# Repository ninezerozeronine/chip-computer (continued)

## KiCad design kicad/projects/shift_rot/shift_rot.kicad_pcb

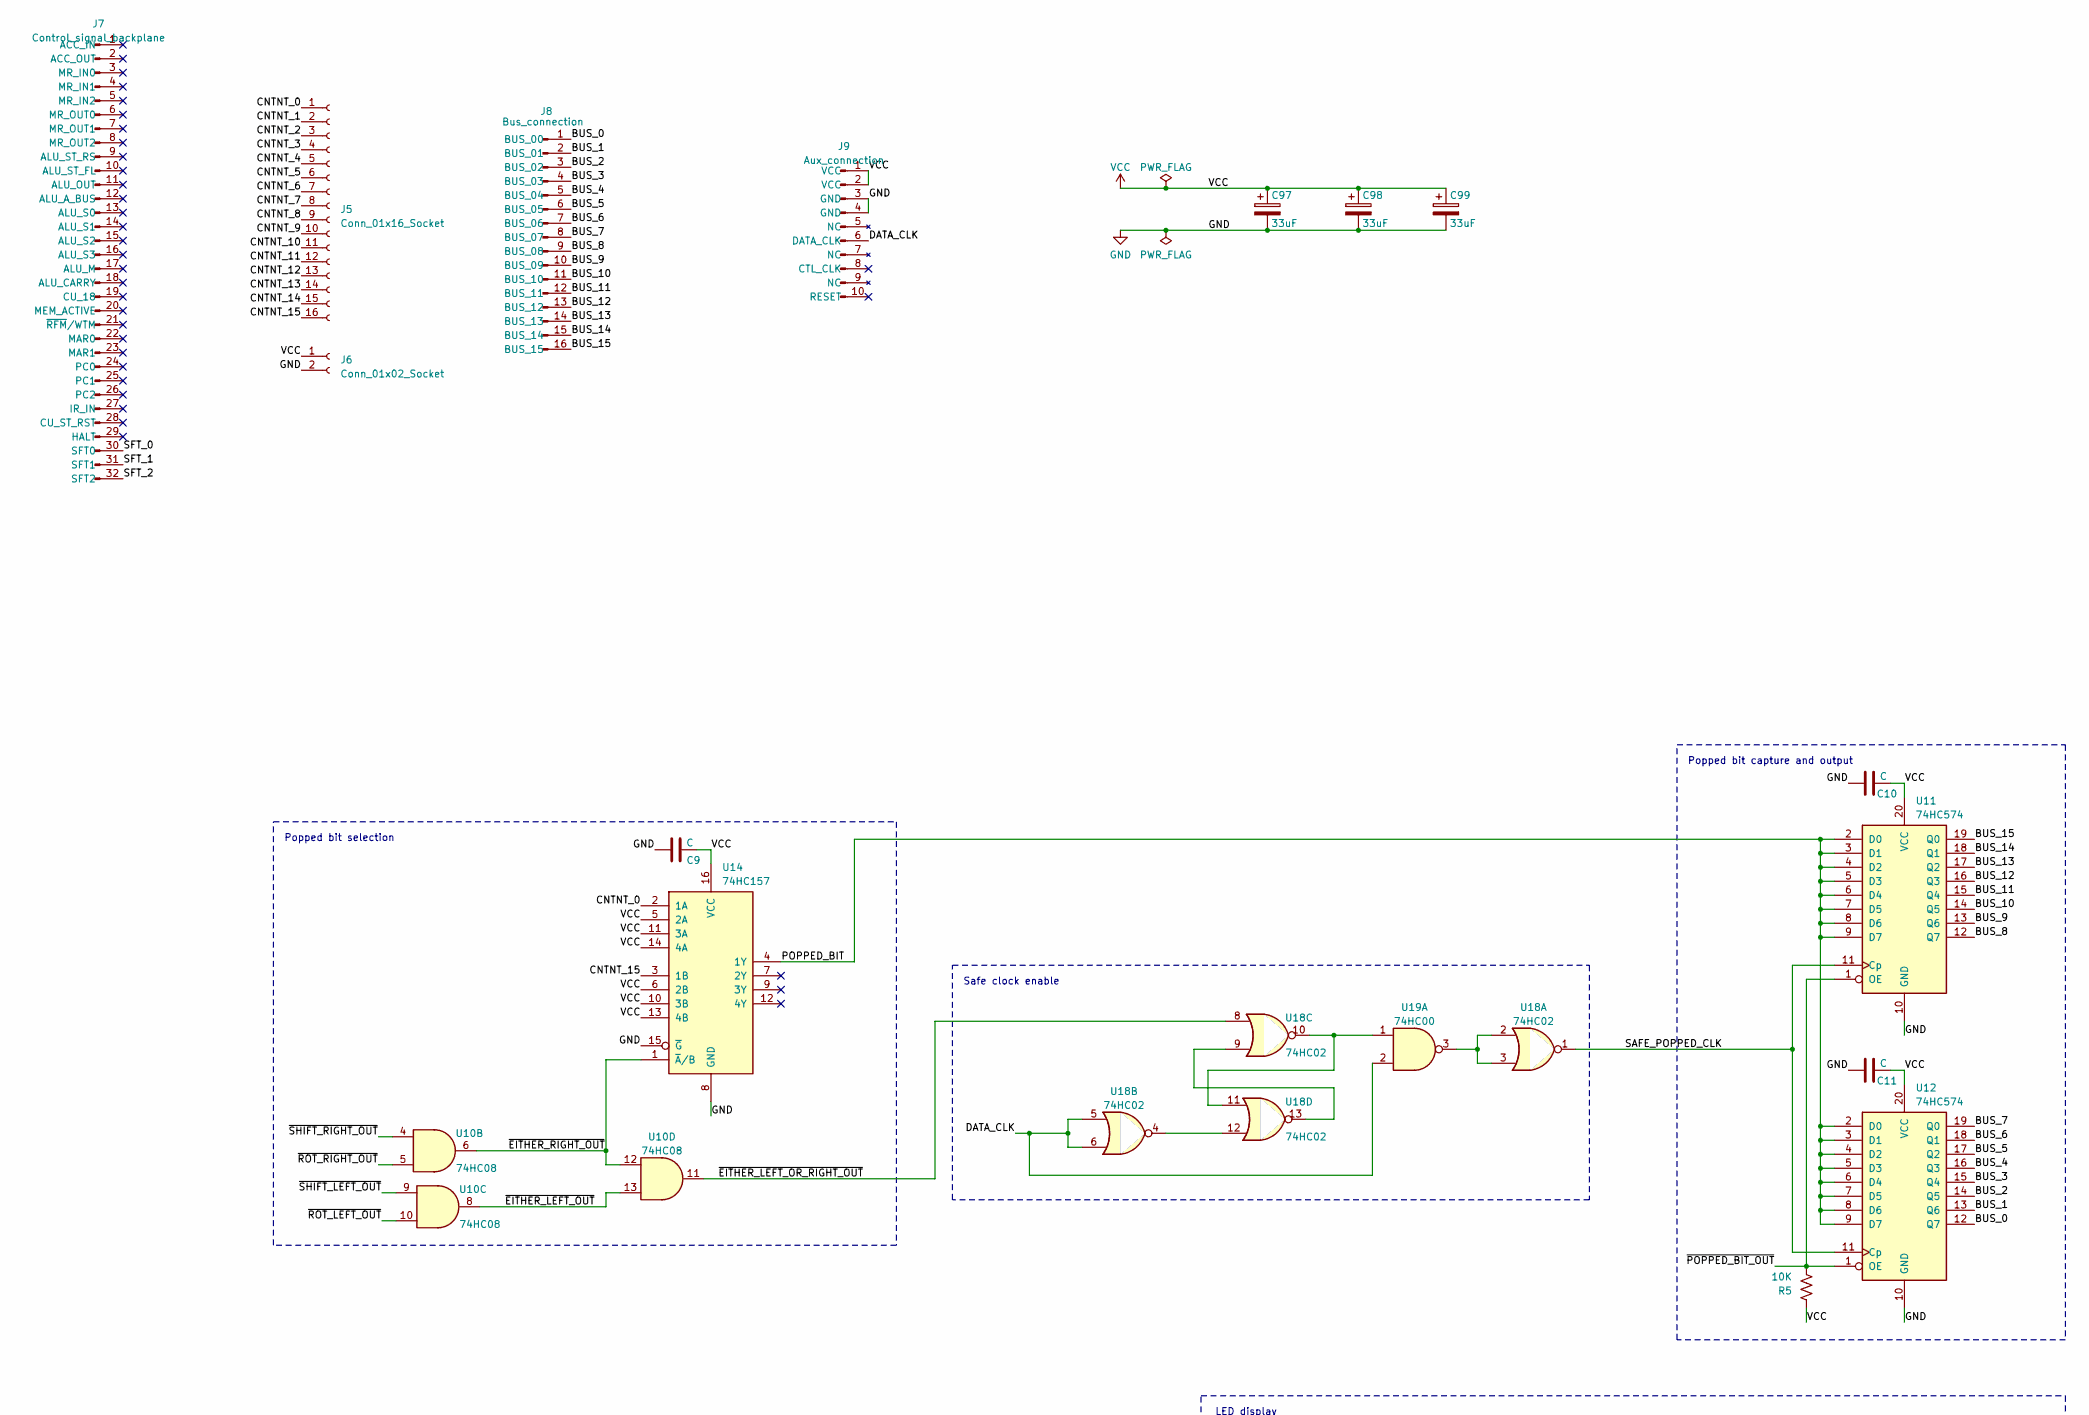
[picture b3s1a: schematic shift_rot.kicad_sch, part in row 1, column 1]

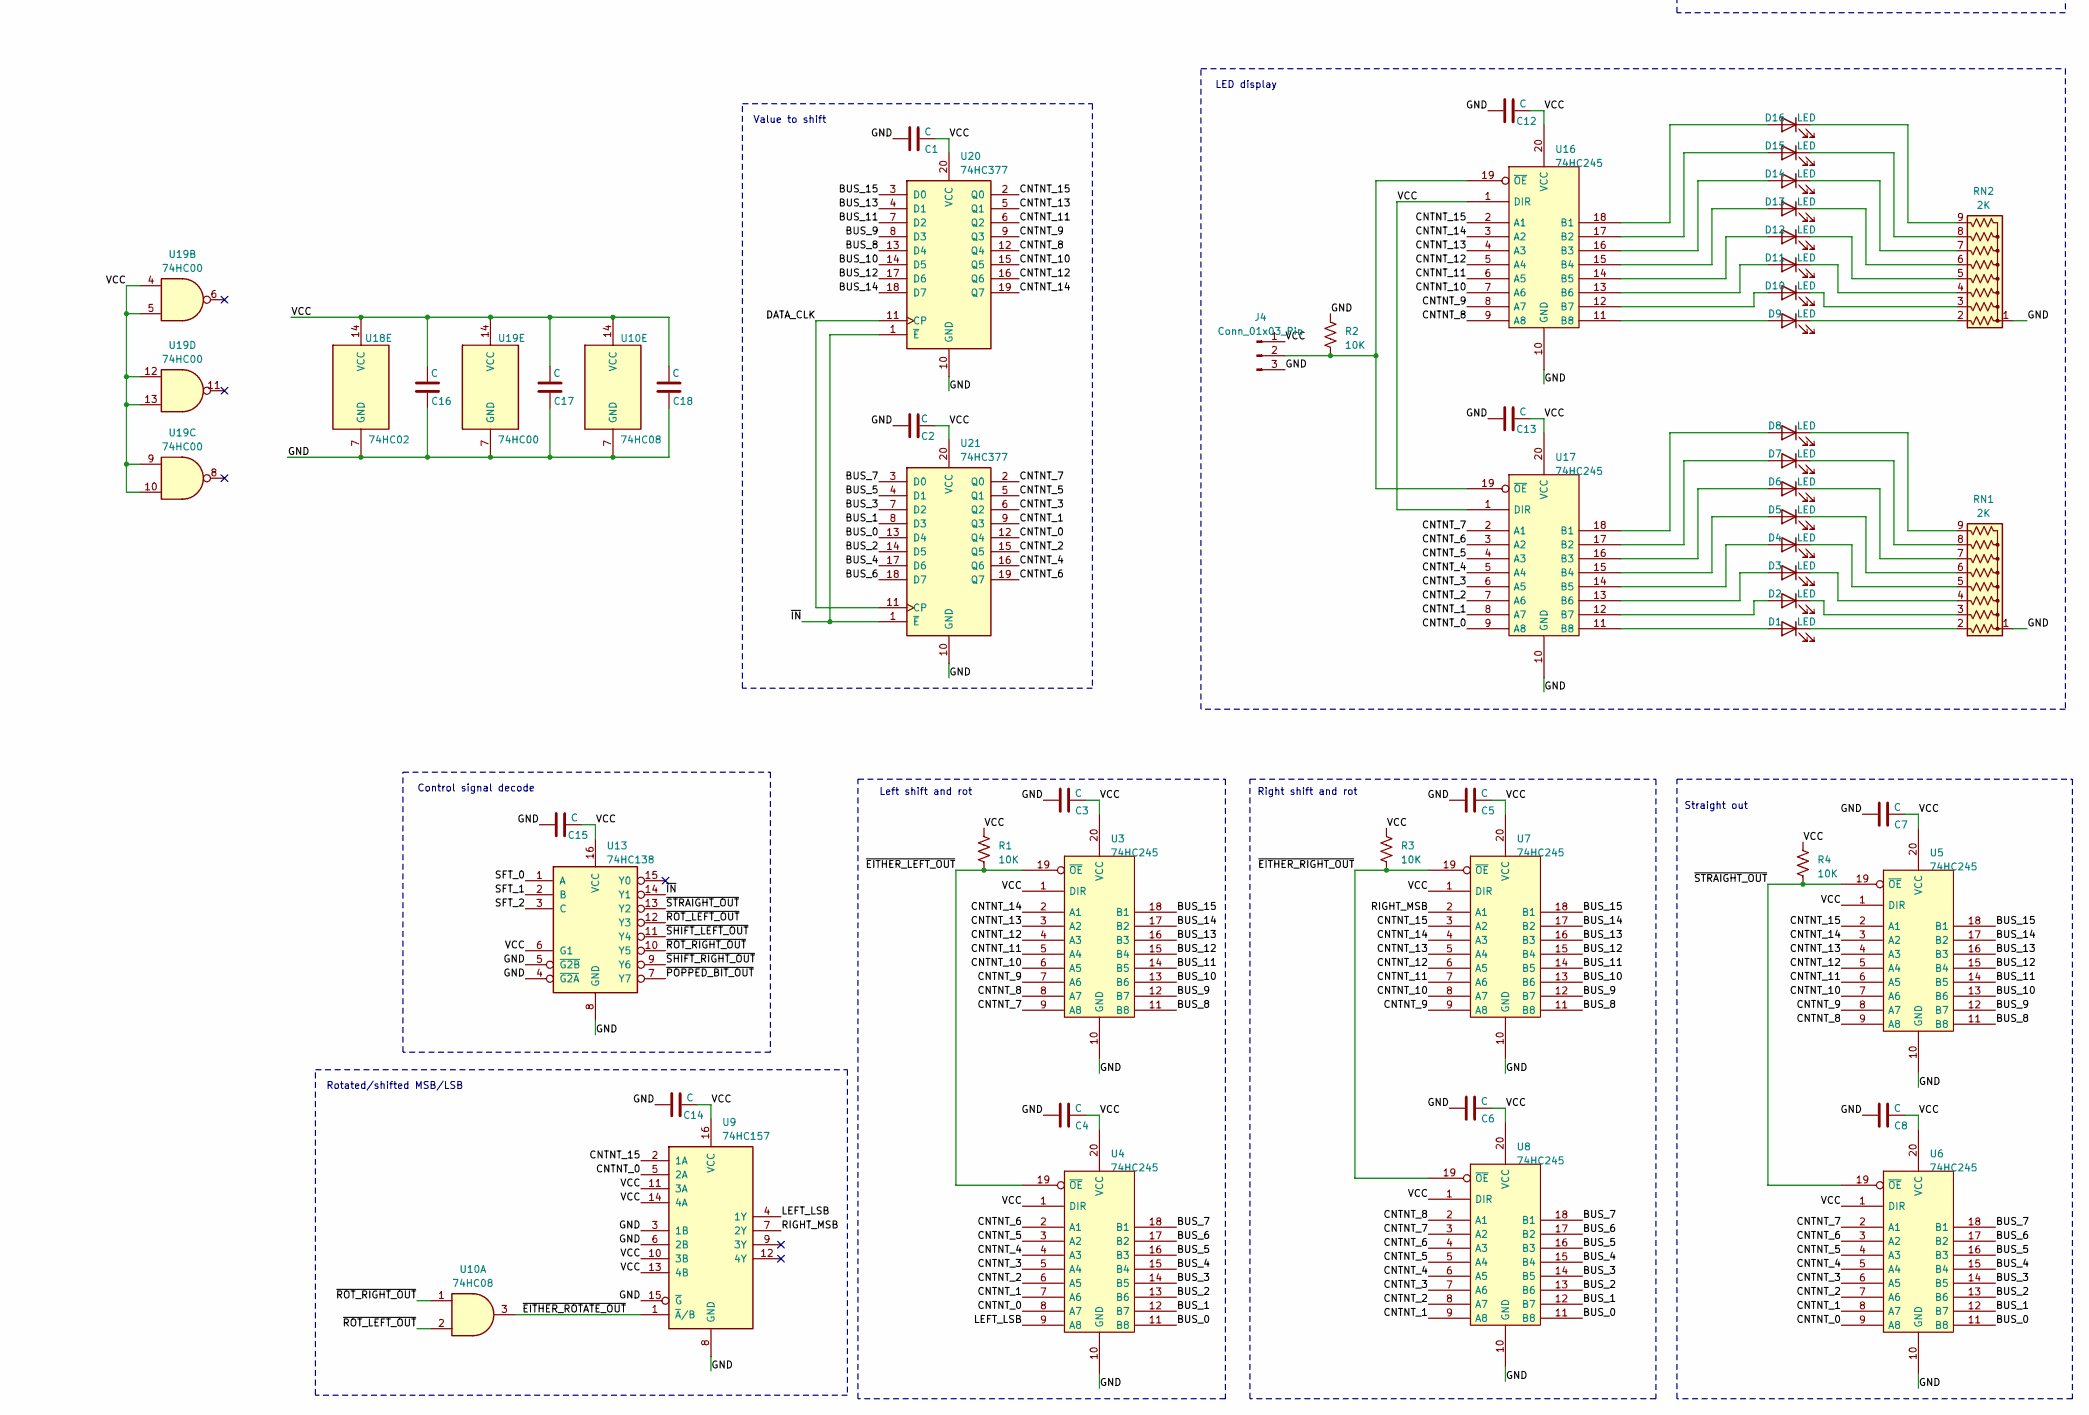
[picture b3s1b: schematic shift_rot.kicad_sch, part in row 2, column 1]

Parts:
C1, C2, C3, C4, C5, C6, C7, C8, C9, C10, C11, C12, C13, C14, C15, C16, C17, C18: C; C_Disc_D5.0mm_W2.5mm_P5.00mm
C97, C98, C99: 33uF; CP_Radial_D6.3mm_P2.50mm
D1, D2, D3, D4, D5, D6, D7, D8, D9, D10, D11, D12, D13, D14, D15, D16: LED; LED_D5.0mm_Horizontal_O3.81mm_Z3.0mm
J4: Conn_01x03_Pin; PinHeader_1x03_P2.54mm_Horizontal
J5: Conn_01x16_Socket; PinSocket_1x16_P2.54mm_Horizontal
J6: Conn_01x02_Socket; PinSocket_1x02_P2.54mm_Horizontal
J7: Control_signal_backplane; backplane-connector-single-row-annotated
J8: Bus_connection; bus-connection
J9: Aux_connection; aux-connection
R1, R2, R3, R4, R5: 10K; R_Axial_DIN0207_L6.3mm_D2.5mm_P10.16mm_Horizontal
RN1, RN2: 2K; R_Array_SIP9
U3, U4, U5, U6, U7, U8, U16, U17: 74HC245; DIP-20_W7.62mm_Socket
U9, U14: 74HC157; DIP-16_W7.62mm_Socket
U10: 74HC08; DIP-14_W7.62mm_Socket
U11, U12: 74HC574; DIP-20_W7.62mm_Socket
U13: 74HC138; DIP-16_W7.62mm_Socket
U18: 74HC02; DIP-14_W7.62mm_Socket
U19: 74HC00; DIP-14_W7.62mm_Socket
U20, U21: 74HC377; DIP-20_W7.62mm_Socket

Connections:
/BUS_0: J8.1 (BUS_00), U4.11 (B8), U6.11 (B8), U8.11 (B8), U12.12 (Q7), U21.13 (D4)
/BUS_1: J8.2 (BUS_01), U4.12 (B7), U6.12 (B7), U8.12 (B7), U12.13 (Q6), U21.8 (D3)
/BUS_2: J8.3 (BUS_02), U4.13 (B6), U6.13 (B6), U8.13 (B6), U12.14 (Q5), U21.14 (D5)
/BUS_3: J8.4 (BUS_03), U4.14 (B5), U6.14 (B5), U8.14 (B5), U12.15 (Q4), U21.7 (D2)
/BUS_4: J8.5 (BUS_04), U4.15 (B4), U6.15 (B4), U8.15 (B4), U12.16 (Q3), U21.17 (D6)
/BUS_5: J8.6 (BUS_05), U4.16 (B3), U6.16 (B3), U8.16 (B3), U12.17 (Q2), U21.4 (D1)
/BUS_6: J8.7 (BUS_06), U4.17 (B2), U6.17 (B2), U8.17 (B2), U12.18 (Q1), U21.18 (D7)
/BUS_7: J8.8 (BUS_07), U4.18 (B1), U6.18 (B1), U8.18 (B1), U12.19 (Q0), U21.3 (D0)
/BUS_8: J8.9 (BUS_08), U3.11 (B8), U5.11 (B8), U7.11 (B8), U11.12 (Q7), U20.13 (D4)
/BUS_9: J8.10 (BUS_09), U3.12 (B7), U5.12 (B7), U7.12 (B7), U11.13 (Q6), U20.8 (D3)
/BUS_10: J8.11 (BUS_10), U3.13 (B6), U5.13 (B6), U7.13 (B6), U11.14 (Q5), U20.14 (D5)
/BUS_11: J8.12 (BUS_11), U3.14 (B5), U5.14 (B5), U7.14 (B5), U11.15 (Q4), U20.7 (D2)
/BUS_12: J8.13 (BUS_12), U3.15 (B4), U5.15 (B4), U7.15 (B4), U11.16 (Q3), U20.17 (D6)
/BUS_13: J8.14 (BUS_13), U3.16 (B3), U5.16 (B3), U7.16 (B3), U11.17 (Q2), U20.4 (D1)
/BUS_14: J8.15 (BUS_14), U3.17 (B2), U5.17 (B2), U7.17 (B2), U11.18 (Q1), U20.18 (D7)
/BUS_15: J8.16 (BUS_15), U3.18 (B1), U5.18 (B1), U7.18 (B1), U11.19 (Q0), U20.3 (D0)
/CNTNT_0: J5.1, U4.8 (A7), U6.9 (A8), U9.5 (2A), U14.2 (1A), U17.9 (A8), U21.12 (Q4)
/CNTNT_1: J5.2, U4.7 (A6), U6.8 (A7), U8.9 (A8), U17.8 (A7), U21.9 (Q3)
/CNTNT_2: J5.3, U4.6 (A5), U6.7 (A6), U8.8 (A7), U17.7 (A6), U21.15 (Q5)
/CNTNT_3: J5.4, U4.5 (A4), U6.6 (A5), U8.7 (A6), U17.6 (A5), U21.6 (Q2)
/CNTNT_4: J5.5, U4.4 (A3), U6.5 (A4), U8.6 (A5), U17.5 (A4), U21.16 (Q6)
/CNTNT_5: J5.6, U4.3 (A2), U6.4 (A3), U8.5 (A4), U17.4 (A3), U21.5 (Q1)
/CNTNT_6: J5.7, U4.2 (A1), U6.3 (A2), U8.4 (A3), U17.3 (A2), U21.19 (Q7)
/CNTNT_7: J5.8, U3.9 (A8), U6.2 (A1), U8.3 (A2), U17.2 (A1), U21.2 (Q0)
/CNTNT_8: J5.9, U3.8 (A7), U5.9 (A8), U8.2 (A1), U16.9 (A8), U20.12 (Q4)
/CNTNT_9: J5.10, U3.7 (A6), U5.8 (A7), U7.9 (A8), U16.8 (A7), U20.9 (Q3)
/CNTNT_10: J5.11, U3.6 (A5), U5.7 (A6), U7.8 (A7), U16.7 (A6), U20.15 (Q5)
/CNTNT_11: J5.12, U3.5 (A4), U5.6 (A5), U7.7 (A6), U16.6 (A5), U20.6 (Q2)
/CNTNT_12: J5.13, U3.4 (A3), U5.5 (A4), U7.6 (A5), U16.5 (A4), U20.16 (Q6)
/CNTNT_13: J5.14, U3.3 (A2), U5.4 (A3), U7.5 (A4), U16.4 (A3), U20.5 (Q1)
/CNTNT_14: J5.15, U3.2 (A1), U5.3 (A2), U7.4 (A3), U16.3 (A2), U20.19 (Q7)
/CNTNT_15: J5.16, U5.2 (A1), U7.3 (A2), U9.2 (1A), U14.3 (1B), U16.2 (A1), U20.2 (Q0)
/DATA_CLK: J9.6 (DATA_CLK), U18.5, U18.6, U19.2, U20.11 (CP), U21.11 (CP)
/LEFT_LSB: U4.9 (A8), U9.4 (1Y)
/POPPED_BIT: U11.2 (D0), U11.3 (D1), U11.4 (D2), U11.5 (D3), U11.6 (D4), U11.7 (D5), U11.8 (D6), U11.9 (D7), U12.2 (D0), U12.3 (D1), U12.4 (D2), U12.5 (D3), U12.6 (D4), U12.7 (D5), U12.8 (D6), U12.9 (D7), U14.4 (1Y)
/RIGHT_MSB: U7.2 (A1), U9.7 (2Y)
/SAFE_POPPED_CLK: U11.11 (Cp), U12.11 (Cp), U18.1
/SFT_0: J7.30 (SFT0), U13.1 (A)
/SFT_1: J7.31 (SFT1), U13.2 (B)
/SFT_2: J7.32 (SFT2), U13.3 (C)
/~EITHER_LEFT_OR_RIGHT_OUT: U10.11, U18.8
/~EITHER_LEFT_OUT: R1.2, U3.19 (~OE), U4.19 (~OE), U10.8, U10.13
/~EITHER_RIGHT_OUT: R3.2, U7.19 (~OE), U8.19 (~OE), U10.6, U10.12, U14.1 (~A/B)
/~EITHER_ROTATE_OUT: U9.1 (~A/B), U10.3
/~IN: U13.14 (Y1), U20.1 (~E), U21.1 (~E)
/~POPPED_BIT_OUT: R5.2, U11.1 (OE), U12.1 (OE), U13.7 (Y7)
/~ROT_LEFT_OUT: U10.2, U10.10, U13.12 (Y3)
/~ROT_RIGHT_OUT: U10.1, U10.5, U13.10 (Y5)
/~SHIFT_LEFT_OUT: U10.9, U13.11 (Y4)
/~SHIFT_RIGHT_OUT: U10.4, U13.9 (Y6)
/~STRAIGHT_OUT: R4.2, U5.19 (~OE), U6.19 (~OE), U13.13 (Y2)
GND: C1.1, C2.1, C3.1, C4.1, C5.1, C6.1, C7.1, C8.1, C9.1, C10.1, C11.1, C12.1, C13.1, C14.1, C15.1, C16.1, C17.1, C18.1, C97.2, C98.2, C99.2, J4.3, J6.2, J9.3 (GND), J9.4 (GND), R2.1, RN1.1 (common), RN2.1 (common), U3.10 (GND), U4.10 (GND), U5.10 (GND), U6.10 (GND), U7.10 (GND), U8.10 (GND), U9.3 (1B), U9.6 (2B), U9.8 (GND), U9.15 (~G), U10.7 (GND), U11.10 (GND), U12.10 (GND), U13.4 (~G2A), U13.5 (~G2B), U13.8 (GND), U14.8 (GND), U14.15 (~G), U16.10 (GND), U17.10 (GND), U18.7 (GND), U19.7 (GND), U20.10 (GND), U21.10 (GND)
unnamed: D1.2 (A), U17.11 (B8)
unnamed: D1.1 (K), RN1.2 (R1)
unnamed: D2.2 (A), U17.12 (B7)
unnamed: D2.1 (K), RN1.3 (R2)
unnamed: D3.2 (A), U17.13 (B6)
unnamed: D3.1 (K), RN1.4 (R3)
unnamed: D4.2 (A), U17.14 (B5)
unnamed: D4.1 (K), RN1.5 (R4)
unnamed: D5.2 (A), U17.15 (B4)
unnamed: D5.1 (K), RN1.6 (R5)
unnamed: D6.2 (A), U17.16 (B3)
unnamed: D6.1 (K), RN1.7 (R6)
unnamed: D7.2 (A), U17.17 (B2)
unnamed: D7.1 (K), RN1.8 (R7)
unnamed: D8.2 (A), U17.18 (B1)
unnamed: D8.1 (K), RN1.9 (R8)
unnamed: D9.2 (A), U16.11 (B8)
unnamed: D9.1 (K), RN2.2 (R1)
unnamed: D10.2 (A), U16.12 (B7)
unnamed: D10.1 (K), RN2.3 (R2)
unnamed: D11.2 (A), U16.13 (B6)
unnamed: D11.1 (K), RN2.4 (R3)
unnamed: D12.2 (A), U16.14 (B5)
unnamed: D12.1 (K), RN2.5 (R4)
unnamed: D13.2 (A), U16.15 (B4)
unnamed: D13.1 (K), RN2.6 (R5)
unnamed: D14.2 (A), U16.16 (B3)
unnamed: D14.1 (K), RN2.7 (R6)
unnamed: D15.2 (A), U16.17 (B2)
unnamed: D15.1 (K), RN2.8 (R7)
unnamed: D16.2 (A), U16.18 (B1)
unnamed: D16.1 (K), RN2.9 (R8)
unnamed: J4.2, R2.2, U16.19 (~OE), U17.19 (~OE)
unnamed: U18.2, U18.3, U19.3
unnamed: U18.10, U18.11, U19.1
unnamed: U18.4, U18.12
unnamed: U18.9, U18.13
VCC: C1.2, C2.2, C3.2, C4.2, C5.2, C6.2, C7.2, C8.2, C9.2, C10.2, C11.2, C12.2, C13.2, C14.2, C15.2, C16.2, C17.2, C18.2, C97.1, C98.1, C99.1, J4.1, J6.1, J9.1 (VCC), J9.2 (VCC), R1.1, R3.1, R4.1, R5.1, U3.1 (DIR), U3.20 (VCC), U4.1 (DIR), U4.20 (VCC), U5.1 (DIR), U5.20 (VCC), U6.1 (DIR), U6.20 (VCC), U7.1 (DIR), U7.20 (VCC), U8.1 (DIR), U8.20 (VCC), U9.10 (3B), U9.11 (3A), U9.13 (4B), U9.14 (4A), U9.16 (VCC), U10.14 (VCC), U11.20 (VCC), U12.20 (VCC), U13.6 (G1), U13.16 (VCC), U14.5 (2A), U14.6 (2B), U14.10 (3B), U14.11 (3A), U14.13 (4B), U14.14 (4A), U14.16 (VCC), U16.1 (DIR), U16.20 (VCC), U17.1 (DIR), U17.20 (VCC), U18.14 (VCC), U19.4, U19.5, U19.9, U19.10, U19.12, U19.13, U19.14 (VCC), U20.20 (VCC), U21.20 (VCC)

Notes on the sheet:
Control signal decode
Safe clock enable
Value to shift
Rotated/shifted MSB/LSB
Left shift and rot
Straight out
Right shift and rot
LED display
Popped bit capture and output
Popped bit selection

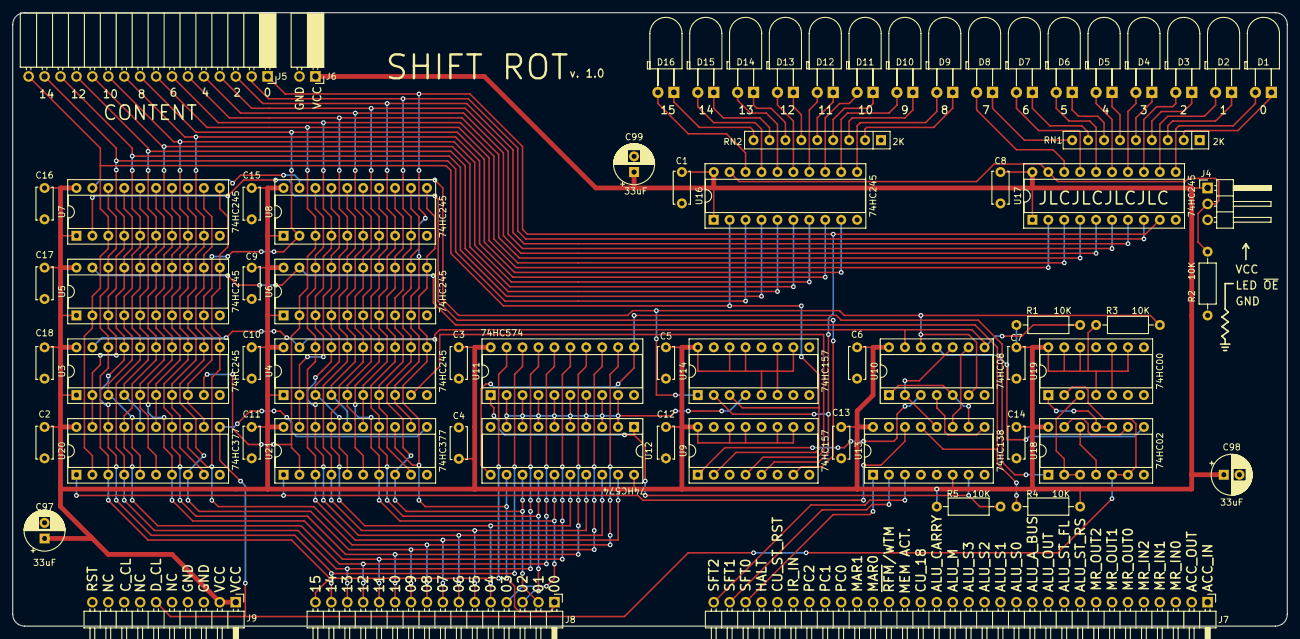
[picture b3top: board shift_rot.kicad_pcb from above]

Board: 2 copper layers, 203.2 x 97.8 mm, 68 parts (0 on the bottom side), 90 nets.

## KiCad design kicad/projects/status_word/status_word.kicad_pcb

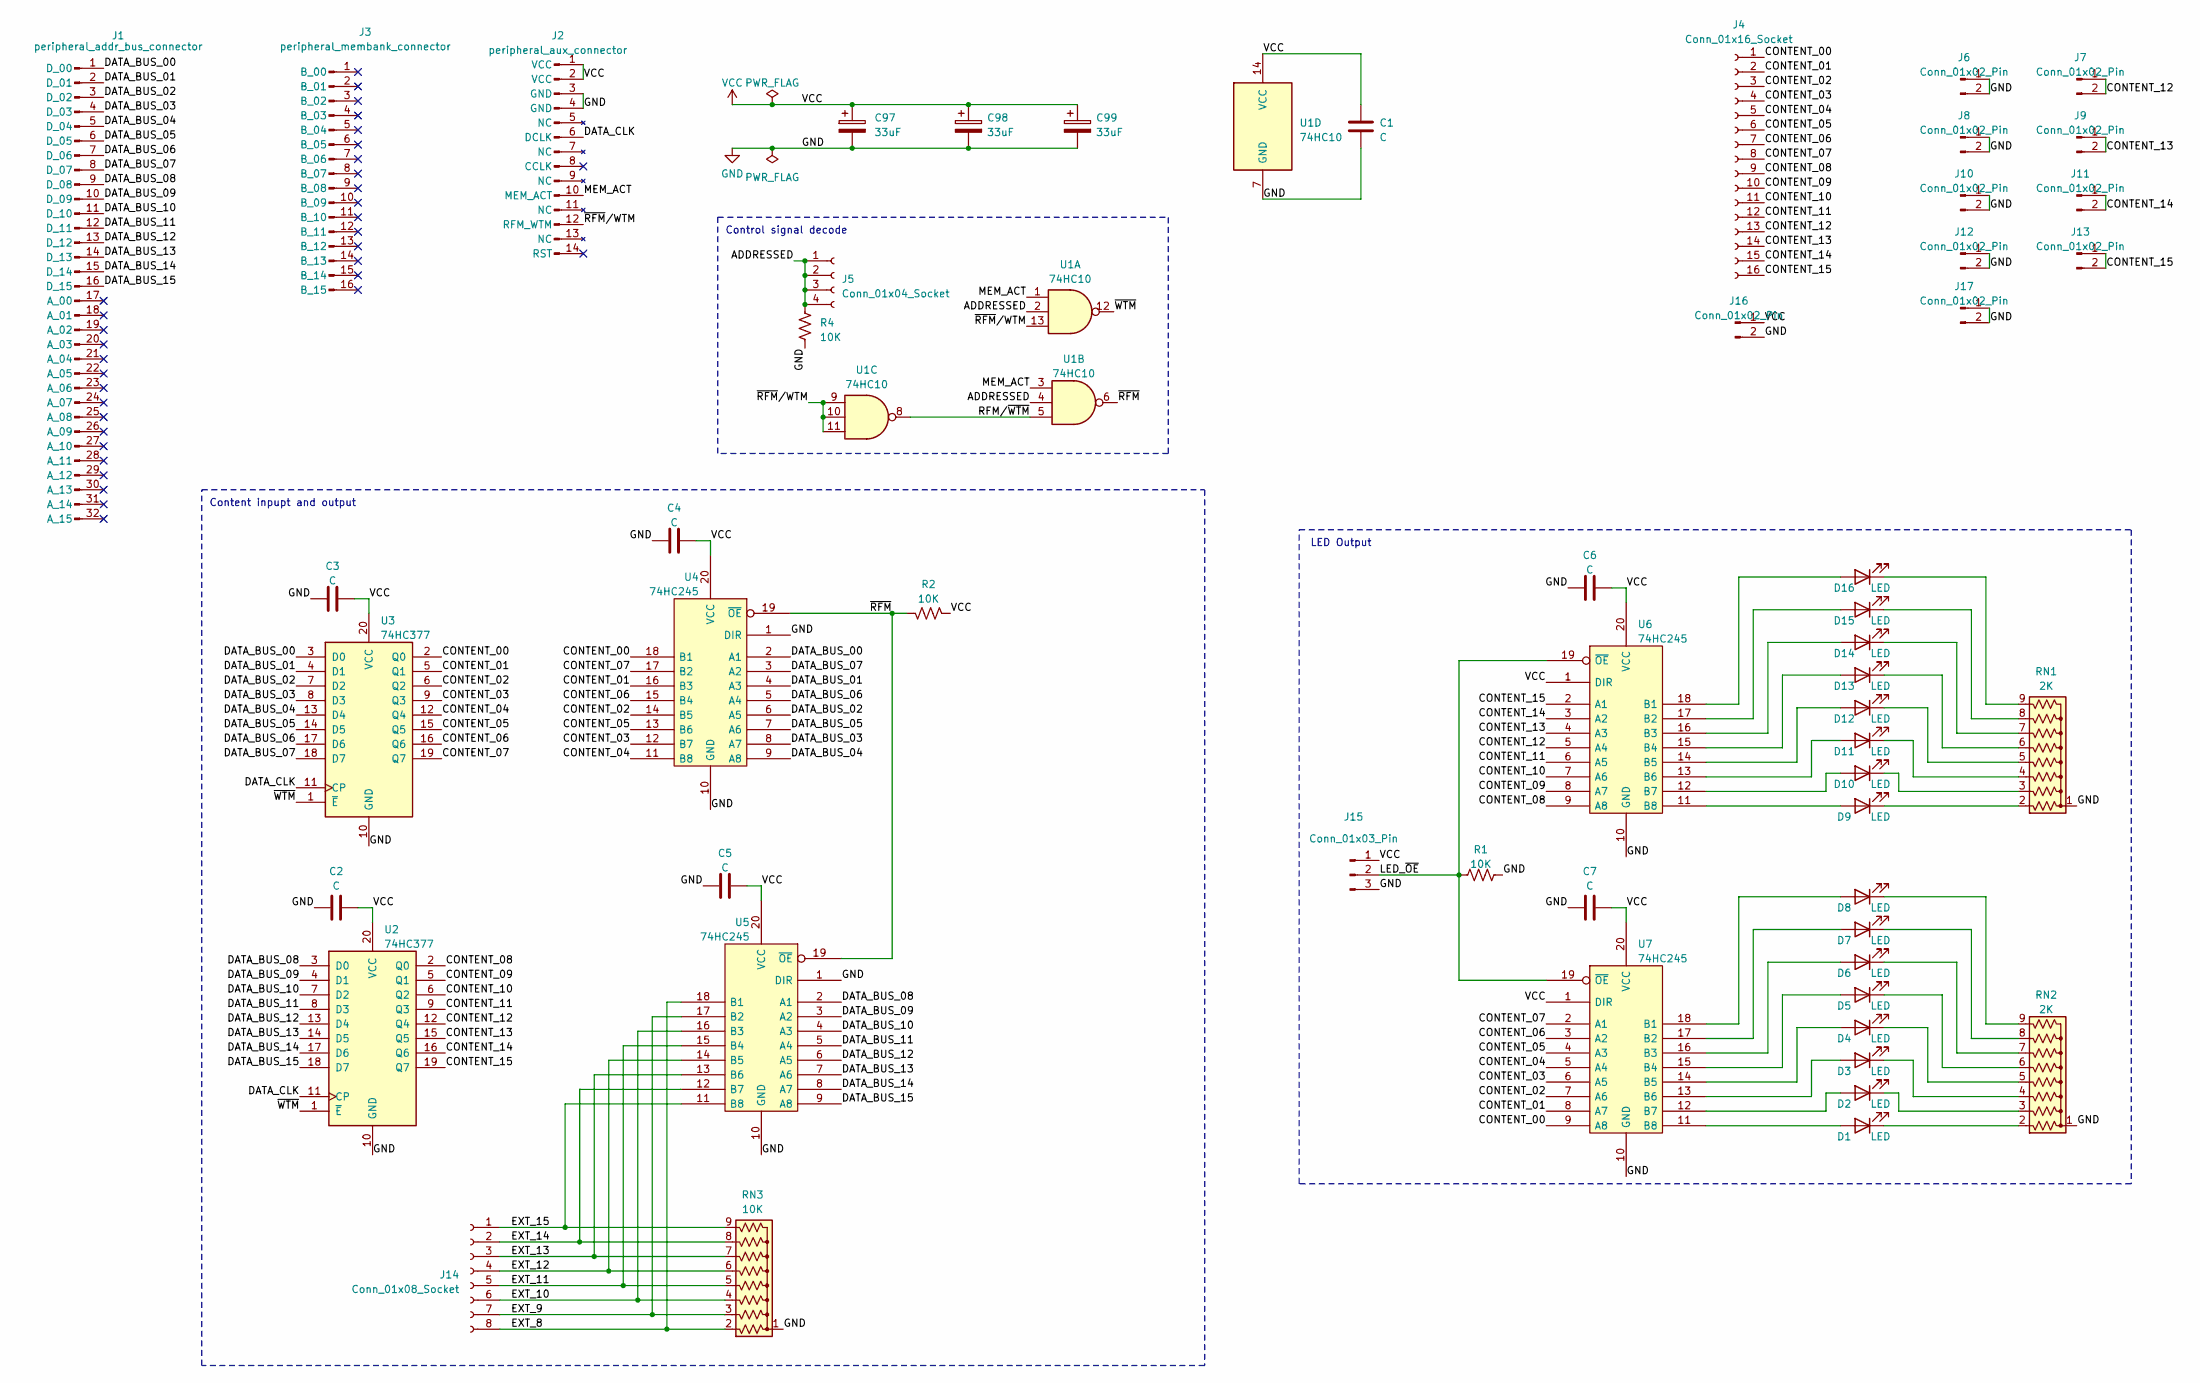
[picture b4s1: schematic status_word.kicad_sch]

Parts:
C1, C2, C3, C4, C5, C6, C7: C; C_Disc_D5.0mm_W2.5mm_P5.00mm
C97, C98, C99: 33uF; CP_Radial_D6.3mm_P2.50mm
D1, D2, D3, D4, D5, D6, D7, D8, D9, D10, D11, D12, D13, D14, D15, D16: LED; LED_D5.0mm_Horizontal_O3.81mm_Z3.0mm
J1: peripheral_addr_bus_connector; peripheral-backplane-data-addr-anno
J2: peripheral_aux_connector; peripheral-backplane-aux
J3: peripheral_membank_connector; peripheral-backplane-membank
J4: Conn_01x16_Socket; PinSocket_1x16_P2.54mm_Horizontal
J5: Conn_01x04_Socket; PinSocket_1x04_P2.54mm_Horizontal
J6, J7, J8, J9, J10, J11, J12, J13, J17: Conn_01x02_Pin; PinHeader_1x02_P2.54mm_Vertical
J14: Conn_01x08_Socket; PinSocket_1x08_P2.54mm_Horizontal
J15: Conn_01x03_Pin; PinHeader_1x03_P2.54mm_Horizontal
J16: Conn_01x02_Pin; PinSocket_1x02_P2.54mm_Horizontal
R1, R2, R4: 10K; R_Axial_DIN0207_L6.3mm_D2.5mm_P10.16mm_Horizontal
RN1, RN2: 2K; R_Array_SIP9
RN3: 10K; R_Array_SIP9
U1: 74HC10; DIP-14_W7.62mm_Socket
U2, U3: 74HC377; DIP-20_W7.62mm_Socket
U4, U5, U6, U7: 74HC245; DIP-20_W7.62mm_Socket

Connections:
/ADDRESSED: J5.1, J5.2, J5.3, J5.4, R4.1, U1.2, U1.4
/CONTENT_00: J4.1, U3.2 (Q0), U4.18 (B1), U7.9 (A8)
/CONTENT_01: J4.2, U3.5 (Q1), U4.16 (B3), U7.8 (A7)
/CONTENT_02: J4.3, U3.6 (Q2), U4.14 (B5), U7.7 (A6)
/CONTENT_03: J4.4, U3.9 (Q3), U4.12 (B7), U7.6 (A5)
/CONTENT_04: J4.5, U3.12 (Q4), U4.11 (B8), U7.5 (A4)
/CONTENT_05: J4.6, U3.15 (Q5), U4.13 (B6), U7.4 (A3)
/CONTENT_06: J4.7, U3.16 (Q6), U4.15 (B4), U7.3 (A2)
/CONTENT_07: J4.8, U3.19 (Q7), U4.17 (B2), U7.2 (A1)
/CONTENT_08: J4.9, U2.2 (Q0), U6.9 (A8)
/CONTENT_09: J4.10, U2.5 (Q1), U6.8 (A7)
/CONTENT_10: J4.11, U2.6 (Q2), U6.7 (A6)
/CONTENT_11: J4.12, U2.9 (Q3), U6.6 (A5)
/CONTENT_12: J4.13, J7.1, J7.2, U2.12 (Q4), U6.5 (A4)
/CONTENT_13: J4.14, J9.1, J9.2, U2.15 (Q5), U6.4 (A3)
/CONTENT_14: J4.15, J11.1, J11.2, U2.16 (Q6), U6.3 (A2)
/CONTENT_15: J4.16, J13.1, J13.2, U2.19 (Q7), U6.2 (A1)
/DATA_BUS_00: J1.1 (D_00), U3.3 (D0), U4.2 (A1)
/DATA_BUS_01: J1.2 (D_01), U3.4 (D1), U4.4 (A3)
/DATA_BUS_02: J1.3 (D_02), U3.7 (D2), U4.6 (A5)
/DATA_BUS_03: J1.4 (D_03), U3.8 (D3), U4.8 (A7)
/DATA_BUS_04: J1.5 (D_04), U3.13 (D4), U4.9 (A8)
/DATA_BUS_05: J1.6 (D_05), U3.14 (D5), U4.7 (A6)
/DATA_BUS_06: J1.7 (D_06), U3.17 (D6), U4.5 (A4)
/DATA_BUS_07: J1.8 (D_07), U3.18 (D7), U4.3 (A2)
/DATA_BUS_08: J1.9 (D_08), U2.3 (D0), U5.2 (A1)
/DATA_BUS_09: J1.10 (D_09), U2.4 (D1), U5.3 (A2)
/DATA_BUS_10: J1.11 (D_10), U2.7 (D2), U5.4 (A3)
/DATA_BUS_11: J1.12 (D_11), U2.8 (D3), U5.5 (A4)
/DATA_BUS_12: J1.13 (D_12), U2.13 (D4), U5.6 (A5)
/DATA_BUS_13: J1.14 (D_13), U2.14 (D5), U5.7 (A6)
/DATA_BUS_14: J1.15 (D_14), U2.17 (D6), U5.8 (A7)
/DATA_BUS_15: J1.16 (D_15), U2.18 (D7), U5.9 (A8)
/DATA_CLK: J2.6 (DCLK), U2.11 (CP), U3.11 (CP)
/EXT_8: J14.8, RN3.2 (R1), U5.18 (B1)
/EXT_9: J14.7, RN3.3 (R2), U5.17 (B2)
/EXT_10: J14.6, RN3.4 (R3), U5.16 (B3)
/EXT_11: J14.5, RN3.5 (R4), U5.15 (B4)
/EXT_12: J14.4, RN3.6 (R5), U5.14 (B5)
/EXT_13: J14.3, RN3.7 (R6), U5.13 (B6)
/EXT_14: J14.2, RN3.8 (R7), U5.12 (B7)
/EXT_15: J14.1, RN3.9 (R8), U5.11 (B8)
/LED_~OE: J15.2, R1.2, U6.19 (~OE), U7.19 (~OE)
/MEM_ACT: J2.10 (MEM_ACT), U1.1, U1.3
/RFM/~WTM: U1.5, U1.8
/~RFM: R2.2, U1.6, U4.19 (~OE), U5.19 (~OE)
/~RFM/WTM: J2.12 (RFM_WTM), U1.9, U1.10, U1.11, U1.13
/~WTM: U1.12, U2.1 (~E), U3.1 (~E)
GND: C1.2, C2.1, C3.1, C4.1, C5.1, C6.1, C7.1, C97.2, C98.2, C99.2, J2.3 (GND), J2.4 (GND), J6.1, J6.2, J8.1, J8.2, J10.1, J10.2, J12.1, J12.2, J15.3, J16.2, J17.1, J17.2, R1.1, R4.2, RN1.1 (common), RN2.1 (common), RN3.1 (common), U1.7 (GND), U2.10 (GND), U3.10 (GND), U4.1 (DIR), U4.10 (GND), U5.1 (DIR), U5.10 (GND), U6.10 (GND), U7.10 (GND)
unnamed: D1.2 (A), U7.11 (B8)
unnamed: D1.1 (K), RN2.2 (R1)
unnamed: D2.2 (A), U7.12 (B7)
unnamed: D2.1 (K), RN2.3 (R2)
unnamed: D3.2 (A), U7.13 (B6)
unnamed: D3.1 (K), RN2.4 (R3)
unnamed: D4.2 (A), U7.14 (B5)
unnamed: D4.1 (K), RN2.5 (R4)
unnamed: D5.2 (A), U7.15 (B4)
unnamed: D5.1 (K), RN2.6 (R5)
unnamed: D6.2 (A), U7.16 (B3)
unnamed: D6.1 (K), RN2.7 (R6)
unnamed: D7.2 (A), U7.17 (B2)
unnamed: D7.1 (K), RN2.8 (R7)
unnamed: D8.2 (A), U7.18 (B1)
unnamed: D8.1 (K), RN2.9 (R8)
unnamed: D9.2 (A), U6.11 (B8)
unnamed: D9.1 (K), RN1.2 (R1)
unnamed: D10.2 (A), U6.12 (B7)
unnamed: D10.1 (K), RN1.3 (R2)
unnamed: D11.2 (A), U6.13 (B6)
unnamed: D11.1 (K), RN1.4 (R3)
unnamed: D12.2 (A), U6.14 (B5)
unnamed: D12.1 (K), RN1.5 (R4)
unnamed: D13.2 (A), U6.15 (B4)
unnamed: D13.1 (K), RN1.6 (R5)
unnamed: D14.2 (A), U6.16 (B3)
unnamed: D14.1 (K), RN1.7 (R6)
unnamed: D15.2 (A), U6.17 (B2)
unnamed: D15.1 (K), RN1.8 (R7)
unnamed: D16.2 (A), U6.18 (B1)
unnamed: D16.1 (K), RN1.9 (R8)
VCC: C1.1, C2.2, C3.2, C4.2, C5.2, C6.2, C7.2, C97.1, C98.1, C99.1, J2.1 (VCC), J2.2 (VCC), J15.1, J16.1, R2.1, U1.14 (VCC), U2.20 (VCC), U3.20 (VCC), U4.20 (VCC), U5.20 (VCC), U6.1 (DIR), U6.20 (VCC), U7.1 (DIR), U7.20 (VCC)

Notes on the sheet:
LED Output
Control signal decode
Content inpupt and output

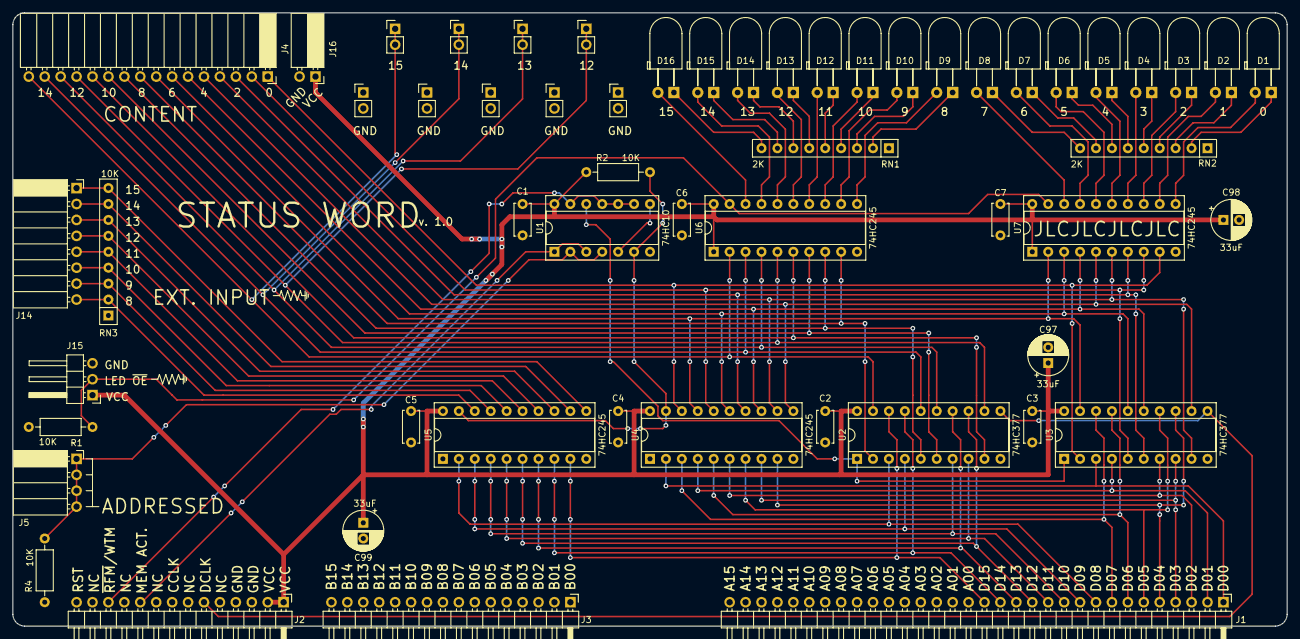
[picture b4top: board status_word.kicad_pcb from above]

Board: 2 copper layers, 203.2 x 97.8 mm, 56 parts (0 on the bottom side), 82 nets.
